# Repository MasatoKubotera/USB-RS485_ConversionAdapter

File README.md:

<html lang="en">
  <head>
    <meta charset="uft-8">
    <meta name="author" content="Masato Kubotera">
  </head>
  <body>
    <h1>USB-RS485 Conversion Adapter Ver. 2.1</h1>
    <h2>About USB-RS485 Conversion Adapter</h2>
    <p>
      The USB-RS485 Conversion Adapter converts communications from the USB interface to the RS-485 interface and can drive KONDO B3M series servo motors.<br>
      <br>
      Note that this is Ver. 2.1. For other versions, please refer to the following repositories.
      <ul>
        <li><a href="https://github.com/MasatoKubotera/USB-RS485_ConversionAdapter_ver2_0">USB-RS485 Conversion Adapter Ver. 2.0</a></li>
      </ul>
      <h2>About Ver. 2.1</h2>
      Ver. 2.1 has a switch and four indicator LEDs to turn the power supply for driving servo motors on and off on the board.
      <!--
      Ver.2.1では、サーボモーター駆動用の電源を基板上でON/OFFするためのスイッチと4つのインジケーターLEDを搭載しています。
      -->
      <table>
        <tr>
          <td>
            <a href="image/brd_top.png">
              <div align="center">
                
              </div>
            </a>
          </td>
          <td>
            <div align="center">
              
            </div>
          </td>
          <td>
            <div align="center">
              
            </div>
          </td>
        </tr>
        <tr>
          <td>
            <div align="center">
              PCB preview image
            </div>
          </td>
          <td>
            <div align="center">
              Actual PCB
            </div>
          </td> 
          <td>
            <div align="center">
              After component mounting
            </div>
          </td>   
        </tr>
      </table>
    </p>
    <h2>Repository Contents</h2>
    <p>
    <dl>
      <dt>\image</dt>
      <dd>PCB preview images and capture of design screen</dd>
      <dt>\libraries</dt>
      <dd>Libraries used in Autodesk Eagle design</dd>
      <dt>Schematic.pdf</dt>
      <dd>Circuit diagram of this product</dd>
      <dt>BOM.txt</dt>
      <dd>Parts lists output from design data</dd>
      <dt>.brd</dt>
      <dd>Board wiring design file by Autodesk Eagle</dd>
      <dt>.sch</dt>
      <dd>Schematic design file by Autodesk Eagle</dd>
      <dt>Gerber_data.zip</dt>
      <dd>Zip folder of Gerber format files for PCB manufacturing requests.</dd>
      <dt>LICENSE</dt>
      <dd>This is a license to use this product. Please confirm before use.</dd>
      <dt>.gitignore</dt>
      <dd>File to exclude cache files from management.</dd>
    </dl>
    </p>
    <h2>Documentation</h2>
      <p>
        <h3>BOM</h3>
          <table>
            <thead>
              <tr>
                <th> Eagle Design Parts # </th>
                <th> Q'ty </th>
                <th> Mfr. Product # </th>
                <th> Supplier </th>
                <th> Description </th>
              </tr>
            </thead>
            <tbody>
              <tr>
                <td> LED1, LED4 </td>
                <td> 2 </td>
                <td> 150060VS86000 </td>
                <td> <a href="https://www.mouser.jp/ProductDetail/Wurth-Elektronik/150060VS86000?qs=GedFDFLaBXGW9qOjzZ1Hmw%3D%3D">Mouser</a> </td>
                <td> Standard LEDs - SMD Green 2V 20mA 573nm 0603 </td>
              </tr>
              <tr>
                <td> LED2, LED3 </td>
                <td> 2 </td>
                <td> 150060YS75000 </td>
                <td> <a href="https://www.mouser.jp/ProductDetail/Wurth-Elektronik/150060YS75000?qs=LlUlMxKIyB0nKmwefHgtZw%3D%3D">Mouser</a> </td>
                <td> Standard LEDs - SMD Yellow 2V 20mA 590nm 0603 </td>
              </tr>
              <tr>
                <td> FL1 </td>
                <td> 1 </td>
                <td> BLM18SD220SN1D </td>
                <td> <a href="https://www.mouser.jp/ProductDetail/Murata-Electronics/BLM18SD220SN1D?qs=glnLrWX4TPq%2Fm8%2FdPQltLg%3D%3D">Mouser</a> </td>
                <td> Ferrite Beads 22 OHM 0603 </td>
              </tr>
              <tr>
                <td> R1, R3, R4 </td>
                <td> 3 </td>
                <td> RC0603FR-101KL </td>
                <td> <a href="https://www.mouser.jp/ProductDetail/YAGEO/RC0603FR-101KL?qs=EiqXWrxQq63MM0wzm69ZKg%3D%3D">Mouser</a> </td>
                <td> Thick Film Resistors - SMD 1 kOhms 100-200mW 1% 0603 </td>
              </tr>
              <tr>
                <td> R2 </td>
                <td> 1 </td>
                <td> RC0603FR-1310KL </td>
                <td> <a href="https://www.mouser.jp/ProductDetail/YAGEO/RC0603FR-1310KL?qs=EiqXWrxQq61KPbFOr8F%252BoA%3D%3D">Mouser</a> </td>
                <td> Thick Film Resistors - SMD 10 kOhms 100-200mW 1% 0604 </td>
              </tr>
              <tr>
                <td> R6 </td>
                <td> 1 </td>
                <td> RC0603FR-10120RL </td>
                <td> <a href="https://www.mouser.jp/ProductDetail/YAGEO/RC0603FR-10120RL?qs=EiqXWrxQq62dlPwl17gZoA%3D%3D">Mouser</a> </td>
                <td> Thick Film Resistors - SMD 120 Ohms 100-200mW 1% 0605 </td>
              </tr>
              <tr>
                <td> R5, R7 </td>
                <td> 2 </td>
                <td> RC0603FR-10680RL </td>
                <td> <a href="https://www.mouser.jp/ProductDetail/YAGEO/RC0603FR-10680RL?qs=kV3c90BOhBEc15QHcN6V1g%3D%3D">Mouser</a> </td>
                <td> Thick Film Resistors - SMD 680 Ohms 100-200mW 1% 0606 </td>
              </tr>
              <tr>
                <td> R8 </td>
                <td> 1 </td>
                <td> RC0603FR-102KL </td>
                <td> <a href="https://www.mouser.jp/ProductDetail/YAGEO/RC0603FR-102KL?qs=EiqXWrxQq61%2FIgp1yfYYog%3D%3D">Mouser</a> </td>
                <td> Thick Film Resistors - SMD 2 kOhms 100-200mW 1% 0607 </td>
              </tr>
              <tr>
                <td> C1 </td>
                <td> 1 </td>
                <td> GRM188B11H103KA01 </td>
                <td> <a href="https://www.google.com/search?q=GRM188B11H103KA01&oq=GRM188B11H103KA01&aqs=chrome.0.69i59.262j0j7&sourceid=chrome&ie=UTF-8">Akizuki</a> </td>
                <td> Multilayer Ceramic Capacitors SMD/SMT 0.01uF 50V 10% 0603 </td>
              </tr>
              <tr>
                <td> C2, C4 </td>
                <td> 2 </td>
                <td> GCM188L81H104K57 </td>
                <td> <a href="https://akizukidenshi.com/catalog/g/gP-16143/">Akizuki</a> </td>
                <td> Multilayer Ceramic Capacitors SMD/SMT 0.1uF 50V 10% 0603 </td>
              </tr>
              <tr>
                <td> C3 </td>
                <td> 1 </td>
                <td> C1608X5R1C475K080AE </td>
                <td> <a href="https://www.mouser.jp/ProductDetail/TDK/C1608X5R1C475K080AE?qs=j%252B1pi9TdxUYQJQlE8Tiuyw%3D%3D">Mouser</a> </td>
                <td> Multilayer Ceramic Capacitors SMD/SMT 4.7uF 16V 10% 0603 </td>
              </tr>
              <tr>
                <td> D1, D2 </td>
                <td> 2 </td>
                <td> CG0603MLC-05E </td>
                <td> <a href="https://www.mouser.jp/ProductDetail/Bourns/CG0603MLC-05E?qs=lDok7oSghXVLNKMK69q%252BFQ%3D%3D">Mouser</a> </td>
                <td> ESD Protectors 5V 0603 </td>
              </tr>
              <tr>
                <td> CH1 </td>
                <td> 1 </td>
                <td> XT60PW-M </td>
                <td> <a href="https://store.shopping.yahoo.co.jp/suzakulab/amass-xt60pw-m.html">Suzaku Lab.</a> </td>
                <td> DC Power Connector, Through Hole, Horizontal, Male, 30A 500V </td>
              </tr>
              <tr>
                <td> CH2 </td>
                <td> 1 </td>
                <td> S4B-XH-A(LF)(SN) </td>
                <td> <a href="https://akizukidenshi.com/catalog/g/gC-12842/">Akizuki</a> </td>
                <td> Connector Header Through Hole, Right Angle 4 position 2.5mm </td>
              </tr>
              <tr>
                <td> USB1 </td>
                <td> 1 </td>
                <td> MUSB-5B-NE-S175 </td>
                <td> <a href="https://akizukidenshi.com/catalog/g/gC-05843/">Akizuki</a> </td>
                <td> Mini USB Connector 5P B type, Female, SMT type, without standoff </td>
              </tr>
              <tr>
                <td> F1 </td>
                <td> 1 </td>
                <td> MF-MSMF050-2 </td>
                <td> <a href="https://www.mouser.jp/ProductDetail/Bourns/MF-MSMF050-2?qs=t3shhpq1i1DZ7OBD5kLNoA%3D%3D">Mouser</a> </td>
                <td> PTC Resettable Fuses 15V .5A-HD 100A MAX </td>
              </tr>
              <tr>
                <td> IC1 </td>
                <td> 1 </td>
                <td> ADM3078E<sup>*1</sup> </td>
                <td> <a href="https://www.mouser.jp/ProductDetail/Analog-Devices/ADM3078EARZ?qs=BpaRKvA4VqGLm2ZAElC2YA%3D%3D">Mouser</a> </td>
                <td> RS-485/RS-422 Transceiver (Half Duplex, 16 Mbps, DE/RE) </td>
              </tr>
              <tr>
                <td> IC2 </td>
                <td> 1 </td>
                <td> FT232RL </td>
                <td> <a href="https://akizukidenshi.com/catalog/g/gI-01739/">Akizuki</a> </td>
                <td> USB Interface IC USB to Serial UART </td>
              </tr>
              <tr>
                <td> S1 </td>
                <td> 1 </td>
                <td> DS-850K-S-ON </td>
                <td> <a href="https://akizukidenshi.com/catalog/g/gP-15740/">Akizuki</a> </td>
                <td> Rocker Switches 125VAC 5A </td>
              </tr>
            </tbody>
          </table>
          <strong>*1</strong> : Since the <a href="https://www.mouser.jp/ProductDetail/Analog-Devices/ADM3078EARZ?qs=BpaRKvA4VqGLm2ZAElC2YA%3D%3D">ADM3078E</a> from Analog Devices was not available at the time of fabrication, the <a href="https://akizukidenshi.com/catalog/g/gI-16211//">MAX3485ED</a> from HTC Korea was used as an alternative.
        <h3>PCB Fabrication</h3>
          PCB(Printed Circuit Board) manufacturing was outsourced to <a href="https://www.elecrow.com/pcb-manufacturing.html">Elecrow</a>.<br>
          The custom specifications are as follows.
          <ul>
            <li>Layer : 2 layers</li>
            <li>Dimensions : 45 x 45</li>
            <li>Different PCB Design : 1eg</li>
            <li>PCB Thickness : 1.6</li>
            <li>PCB Color : Black</li>
            <li>Surface Finish : HASL</li>
            <li>Castellated Hole : No</li>
            <li>Copper Weight : 1oz</li>
            <li>PCB Stencil : Stencil 10cm X 10cm no frame[Top]</li>
          </ul>
          The data used to order fabrication are as follows.
          <ul>
            <li>Eagle design rule : <a href="https://www.elecrow.com/download/Elecrow_PCB_eagle_rule.zip">Elecrow Eagle Design Rule</a></li>
            <li>Eagle CAM file : <a href="https://www.elecrow.com/download/Elecrow_Gerber_Generater_DrillAlign.zip">Elecrow CAM file</a></li>
            <li>Gerber format data : <a href="/Gerber_data.zip">Gerber_data.zip</a></li>
          </ul>
      </p>
    <h2>Contact</h2>
    <p>
    If you have any questions, please contact MasatoKubotera, the product's designer, by E-mail.<br>
    E-mail : <a href="mailto:masatokubotera06@yahoo.co.jp">masatokubotera06@yahoo.co.jp</a>
    </p>
    <h2>License Information</h2>
    <p>
      This product is open source.<br>
      Please review the <a href="/LICENSE">LICENSE file</a> for license information.<br>
      <br>
      <strong>USB-RS485 Conversion Adapter Ver. 2.1</strong> by Masato Kubotera is licensed under a <a href="http://creativecommons.org/licenses/by-nc-sa/4.0/">Creative Commons Attribution-NonCommercial-ShareAlike 4.0 International License</a>.
    </p>    
  </body>
</html>

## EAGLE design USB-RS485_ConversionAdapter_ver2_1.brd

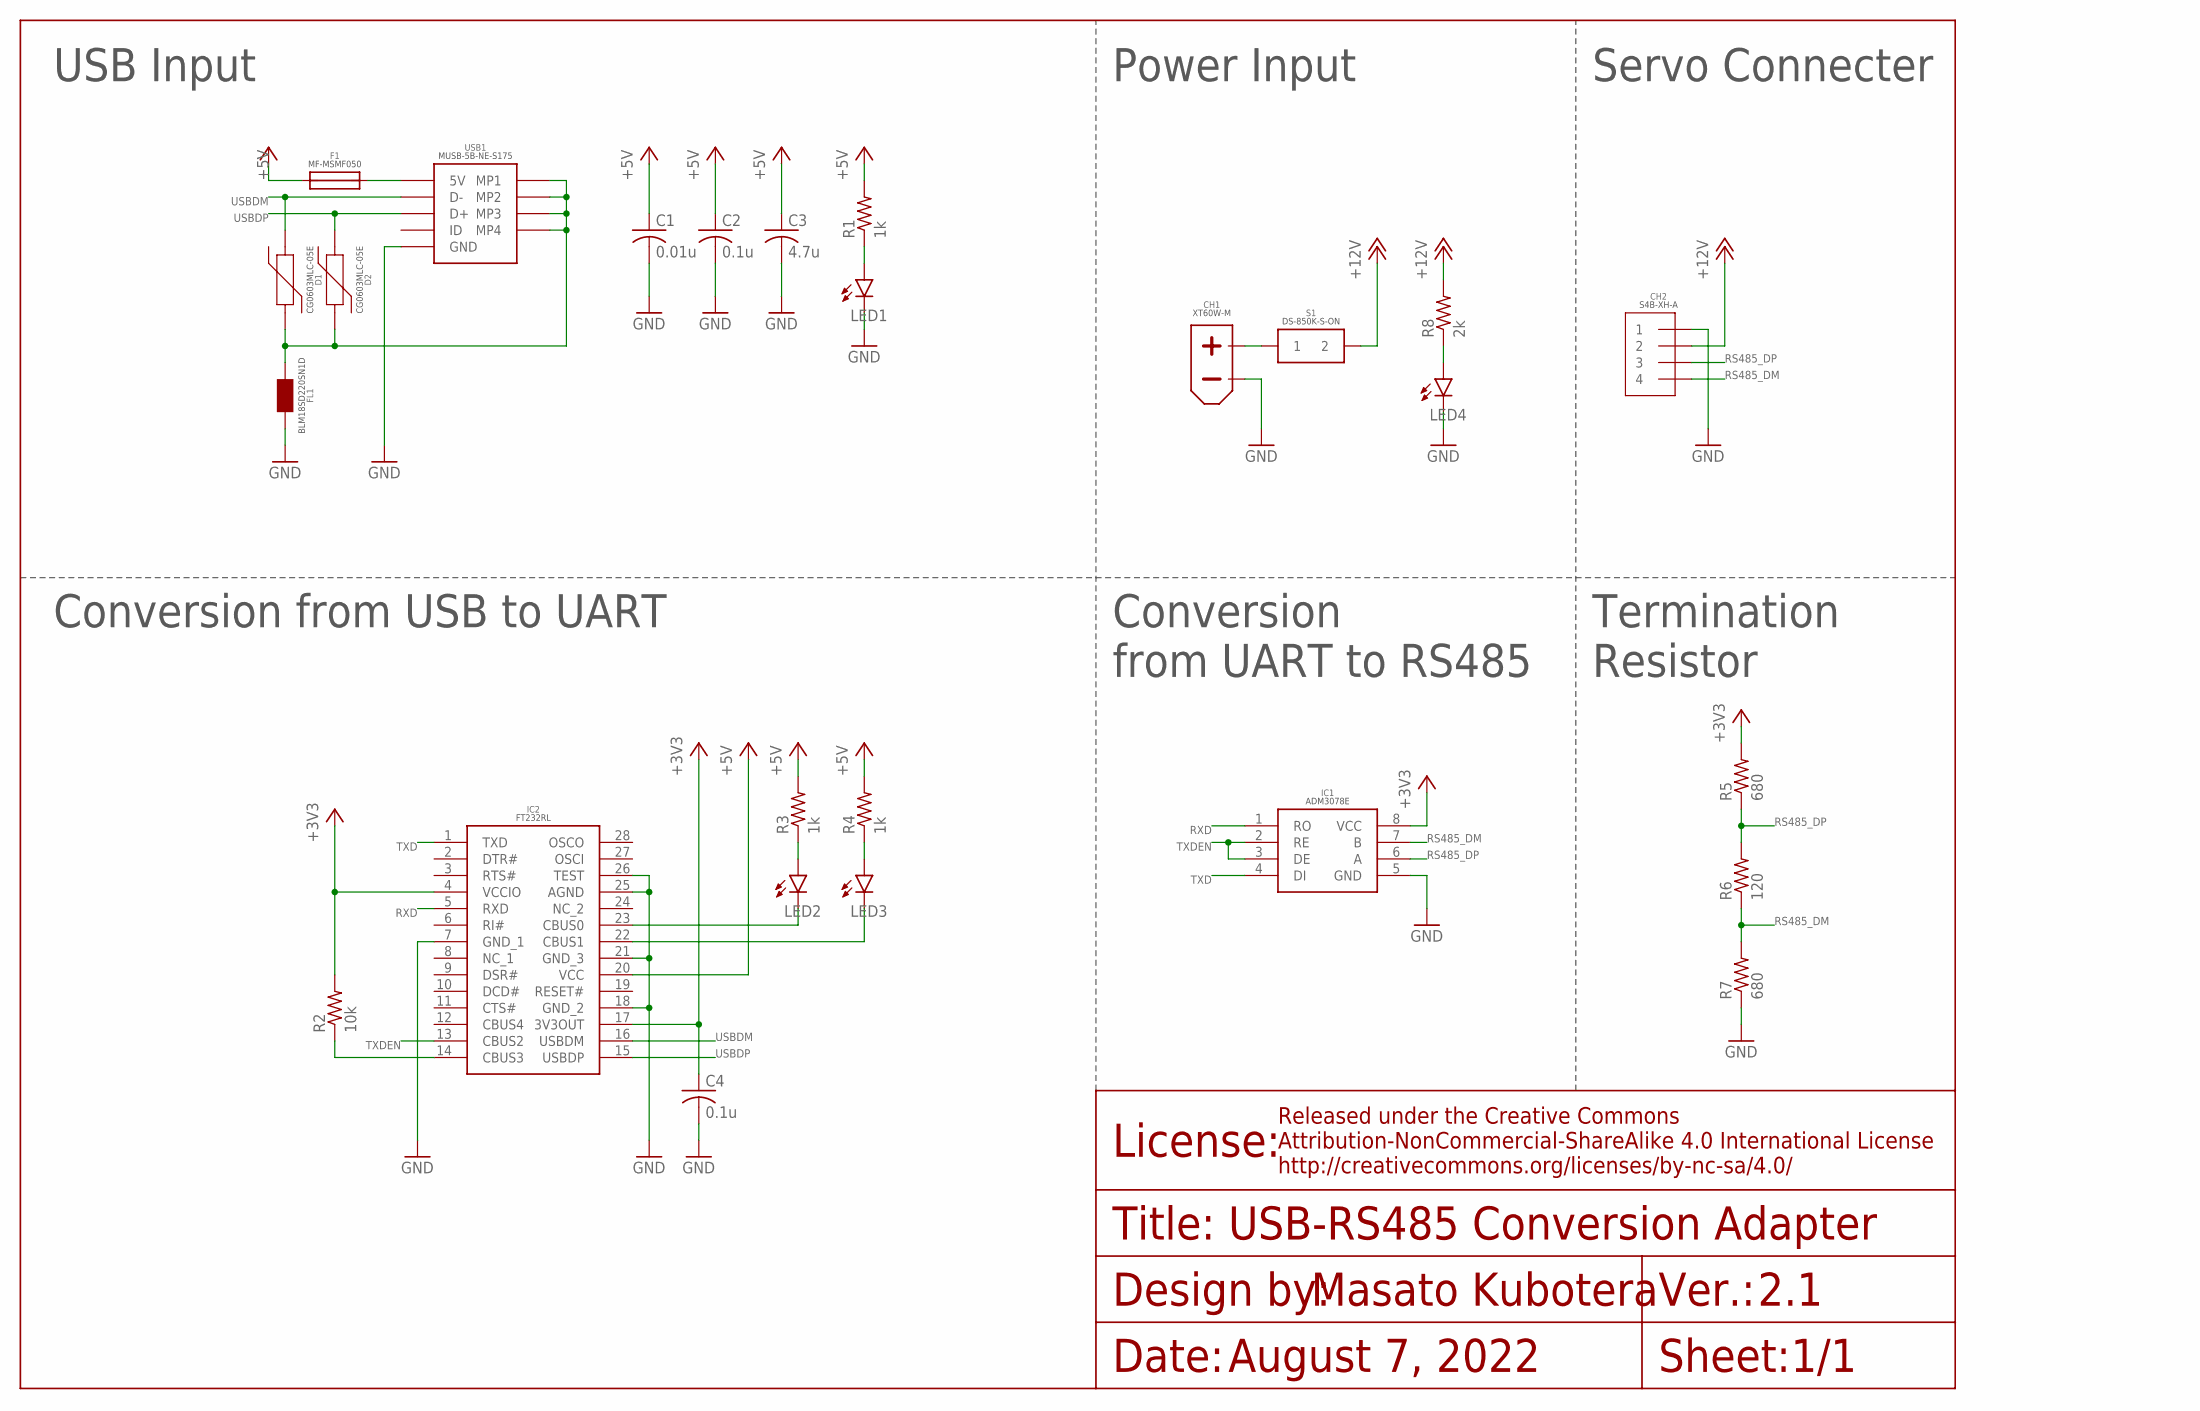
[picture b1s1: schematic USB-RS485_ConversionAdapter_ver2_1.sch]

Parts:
C1: 0.01u; C0603
C2, C4: 0.1u; C0603
C3: 4.7u; C0603
CH1: XT60PW-M
CH2: S4B-XH-A
D1, D2: CG0603MLC-05E
F1: MF-MSMF050
FL1: BLM18SD220SN1D
IC1: ADM3078E
IC2: FT232RL
LED1, LED2, LED3, LED4: LEDSML0603; SML0603
R1, R3, R4: 1k; R0603
R2: 10k; R0603
R5, R7: 680; R0603
R6: 120; R0603
R8: 2k; R0603
S1: DS-850K-S-ON
USB1: MINI_USB_B_SMD

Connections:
5V_LED: LED1.A, R1.1
12V_LED: LED4.A, R8.1
+3V3: C4.1, IC1.8 (VCC), IC2.4 (VCCIO), IC2.17 (3V3OUT), R2.2, R5.2
+5V: C1.1, C2.1, C3.1, F1.1, IC2.20 (VCC), R1.2, R3.2, R4.2
+12V: CH2.2, R8.2, S1.2B (2), S1.2T (2)
BEFORE_+12V: CH1.+, S1.1B (1), S1.1T (1)
B_FUSE_USB_MINI_B: F1.2, USB1.1 (5V)
CBUS0: IC2.23 (CBUS0), LED2.C
CBUS1: IC2.22 (CBUS1), LED3.C
CBUS3: IC2.14 (CBUS3), R2.1
GND: C1.2, C2.2, C3.2, C4.2, CH1.-, CH2.1, FL1.2, IC1.5 (GND), IC2.7 (GND_1), IC2.18 (GND_2), IC2.21 (GND_3), IC2.25 (AGND), IC2.26 (TEST), LED1.C, LED4.C, R7.1, USB1.5 (GND)
RS485_DM: CH2.4, IC1.7 (B), R6.1, R7.2
RS485_DP: CH2.3, IC1.6 (A), R5.1, R6.2
RXD: IC1.1 (RO), IC2.5 (RXD)
RXLED#: LED3.A, R4.1
TXD: IC1.4 (DI), IC2.1 (TXD)
TXDEN: IC1.2 (RE), IC1.3 (DE), IC2.13 (CBUS2)
TXLED#: LED2.A, R3.1
USBDM: D1.1, IC2.16 (USBDM), USB1.2 (D-)
USBDP: D2.1, IC2.15 (USBDP), USB1.3 (D+)
USB_MINI_B_SHIELD: D1.2, D2.2, FL1.1, USB1.MP1, USB1.MP2, USB1.MP3, USB1.MP4

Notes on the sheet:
2.1
1/1
August 7, 2022
USB-RS485 Conversion Adapter
USB Input
Power Input
Servo Connecter
Conversion from USB to UART
Conversion from UART to RS485
Termination Resistor

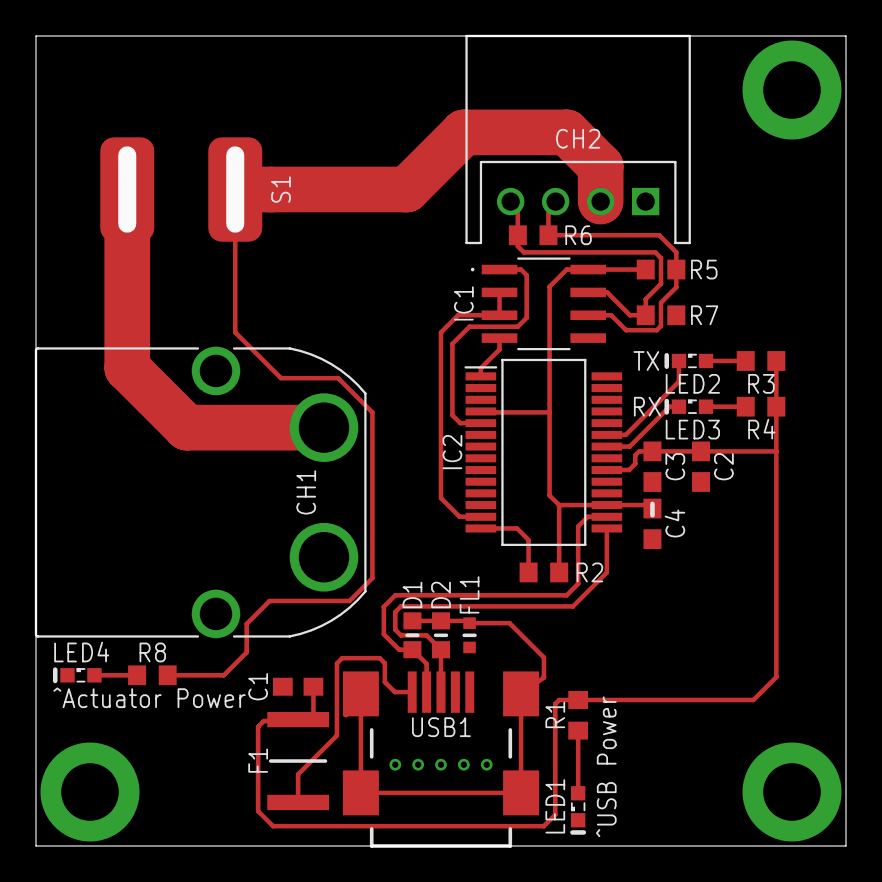
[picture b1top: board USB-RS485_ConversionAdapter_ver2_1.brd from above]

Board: 2 copper layers, 44.0 x 44.0 mm, 26 parts (0 on the bottom side), 21 nets.

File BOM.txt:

Partlist exported from C:/Users/Masato/Desktop/USB-RS485_ConversionAdapter_ver2_1/USB-RS485_ConversionAdapter_ver2_1.sch at 2022/09/28 3:23

Qty Value          Device         Package        Parts                  Description                
4                  LEDSML0603     SML0603        LED1, LED2, LED3, LED4 LED                        
1   0.01u          C-USC0603      C0603          C1                     CAPACITOR, American symbol 
2   0.1u           C-USC0603      C0603          C2, C4                 CAPACITOR, American symbol 
1   10k            R-US_R0603     R0603          R2                     RESISTOR, American symbol  
1   120            R-US_R0603     R0603          R6                     RESISTOR, American symbol  
3   1k             R-US_R0603     R0603          R1, R3, R4             RESISTOR, American symbol  
1   2k             R-US_R0603     R0603          R8                     RESISTOR, American symbol  
1   4.7u           C-USC0603      C0603          C3                     CAPACITOR, American symbol 
2   680            R-US_R0603     R0603          R5, R7                 RESISTOR, American symbol  
1   ADM3078E       ADM3078E       ADM3078E       IC1                                               
1   BLM18SD220SN1D BLM18SD220SN1D BLM18SD220SN1D FL1                                               
2   CG0603MLC-05E  CG0603MLC-05E  CG0603MLC-05E  D1, D2                                            
1   DS-850K-S-ON   DS-850K-S-ON   DS-850K-S-ON   S1                                                
1   FT232RL        FT232RL        FT232RL        IC2                                               
1   MF-MSMF050     MF-MSMF050     MF-MSMF050     F1                                                
1   MINI_USB_B_SMD MINI_USB_B_SMD MINI_USB_B_SMD USB1                                              
1   S4B-XH-A       S4B-XH-A       S4B-XH-A       CH2                                               
1   XT60PW-M       XT60PW-M       XT60PW-M       CH1

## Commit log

2022-09-13 Designed USB-RS485 Conversion Adapter
2022-09-13 Create LICENSE
2022-09-13 add BOM
2022-09-23 Update LICENSE
2022-09-27 Update License and organize data

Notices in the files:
parts and their libraries:
Frame: Released under the Creative Commons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
